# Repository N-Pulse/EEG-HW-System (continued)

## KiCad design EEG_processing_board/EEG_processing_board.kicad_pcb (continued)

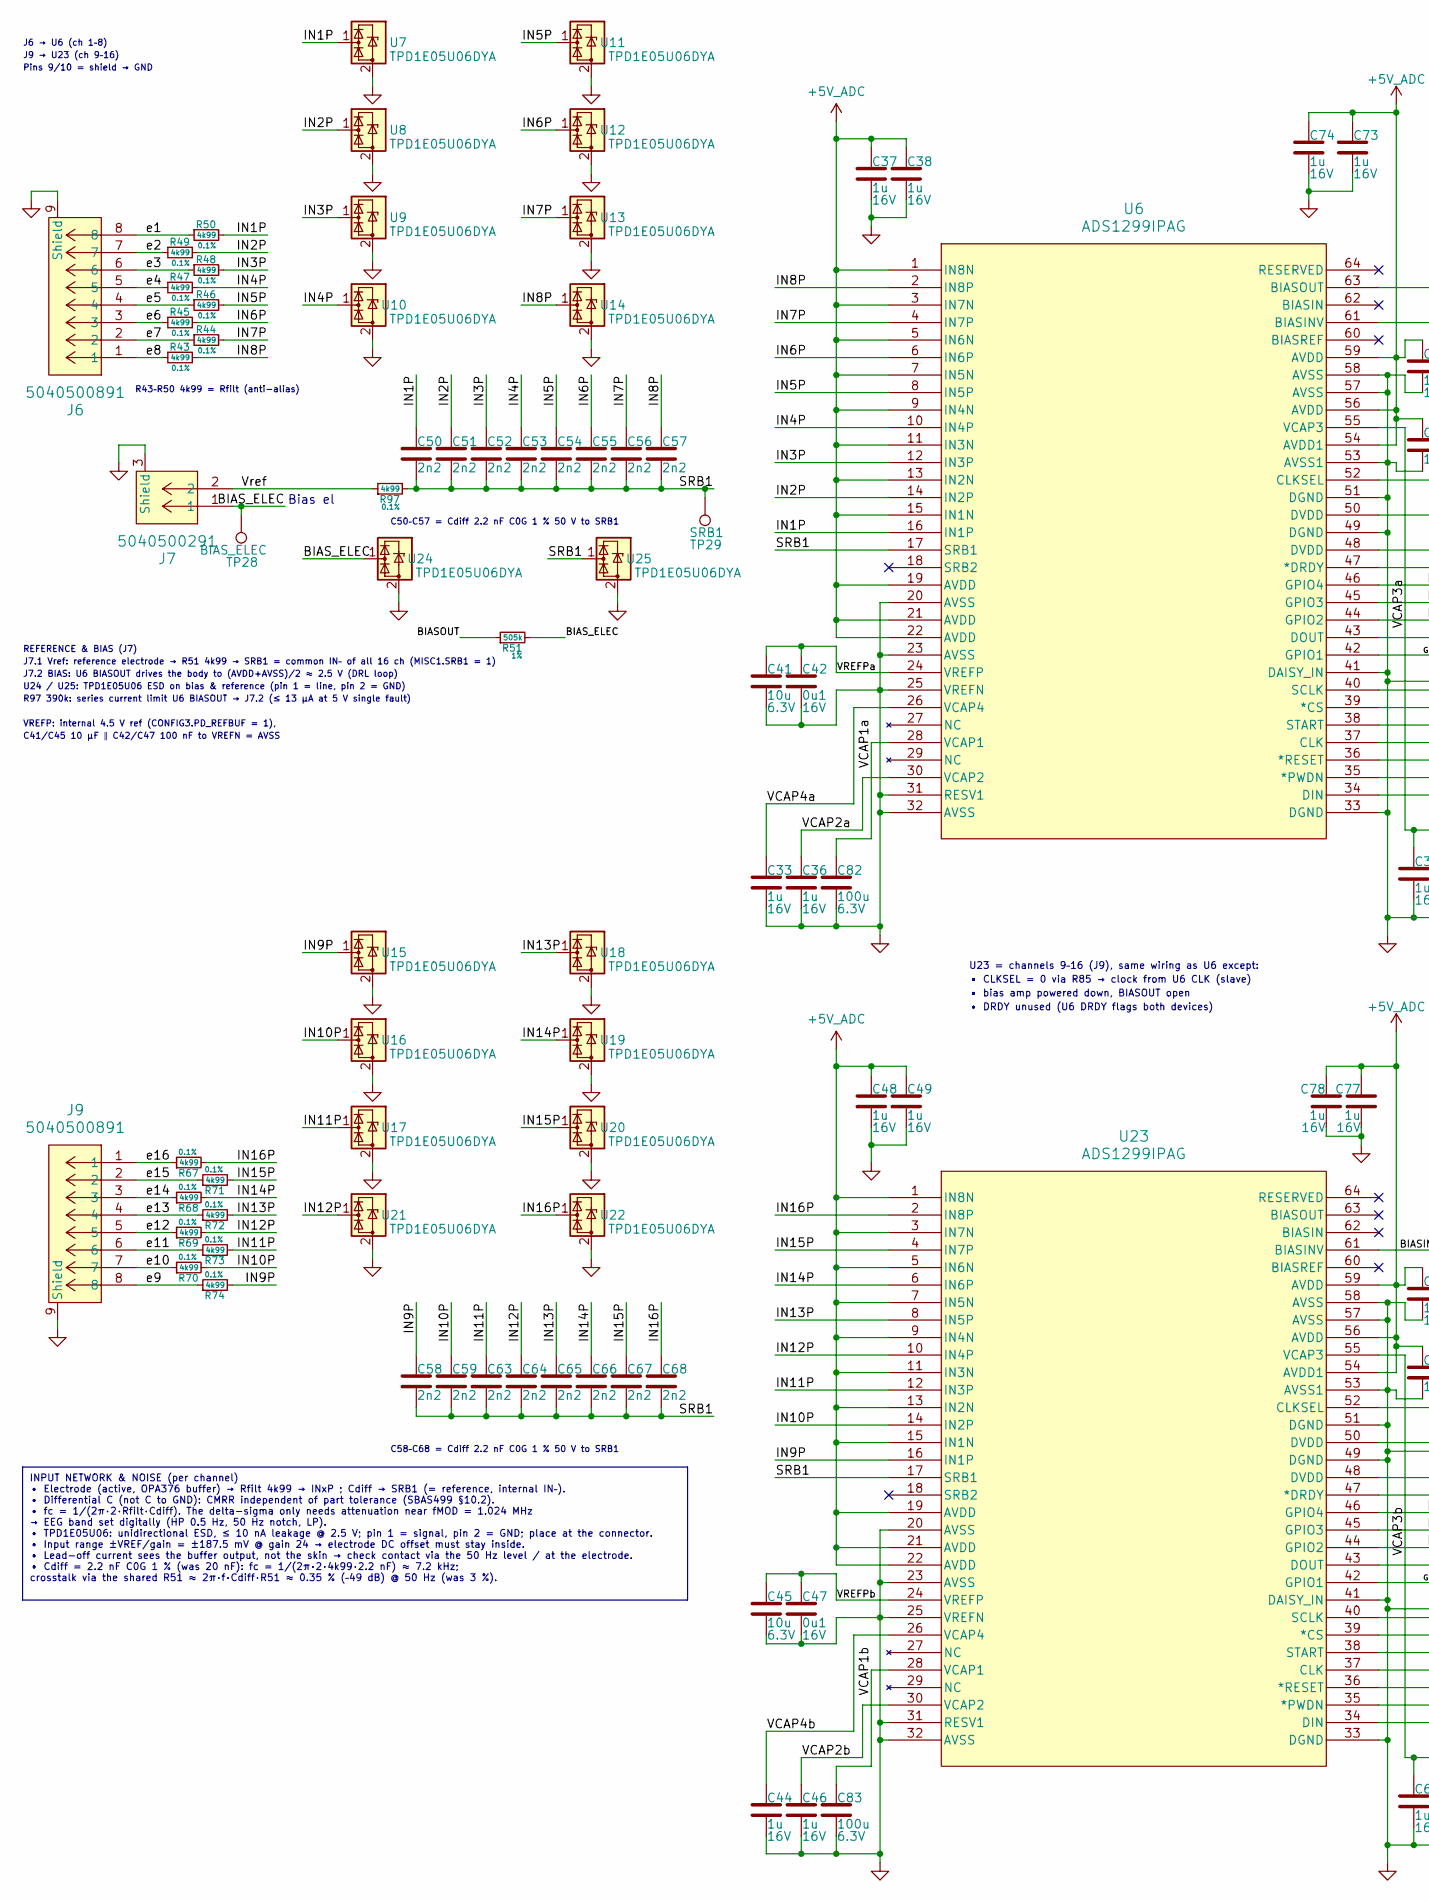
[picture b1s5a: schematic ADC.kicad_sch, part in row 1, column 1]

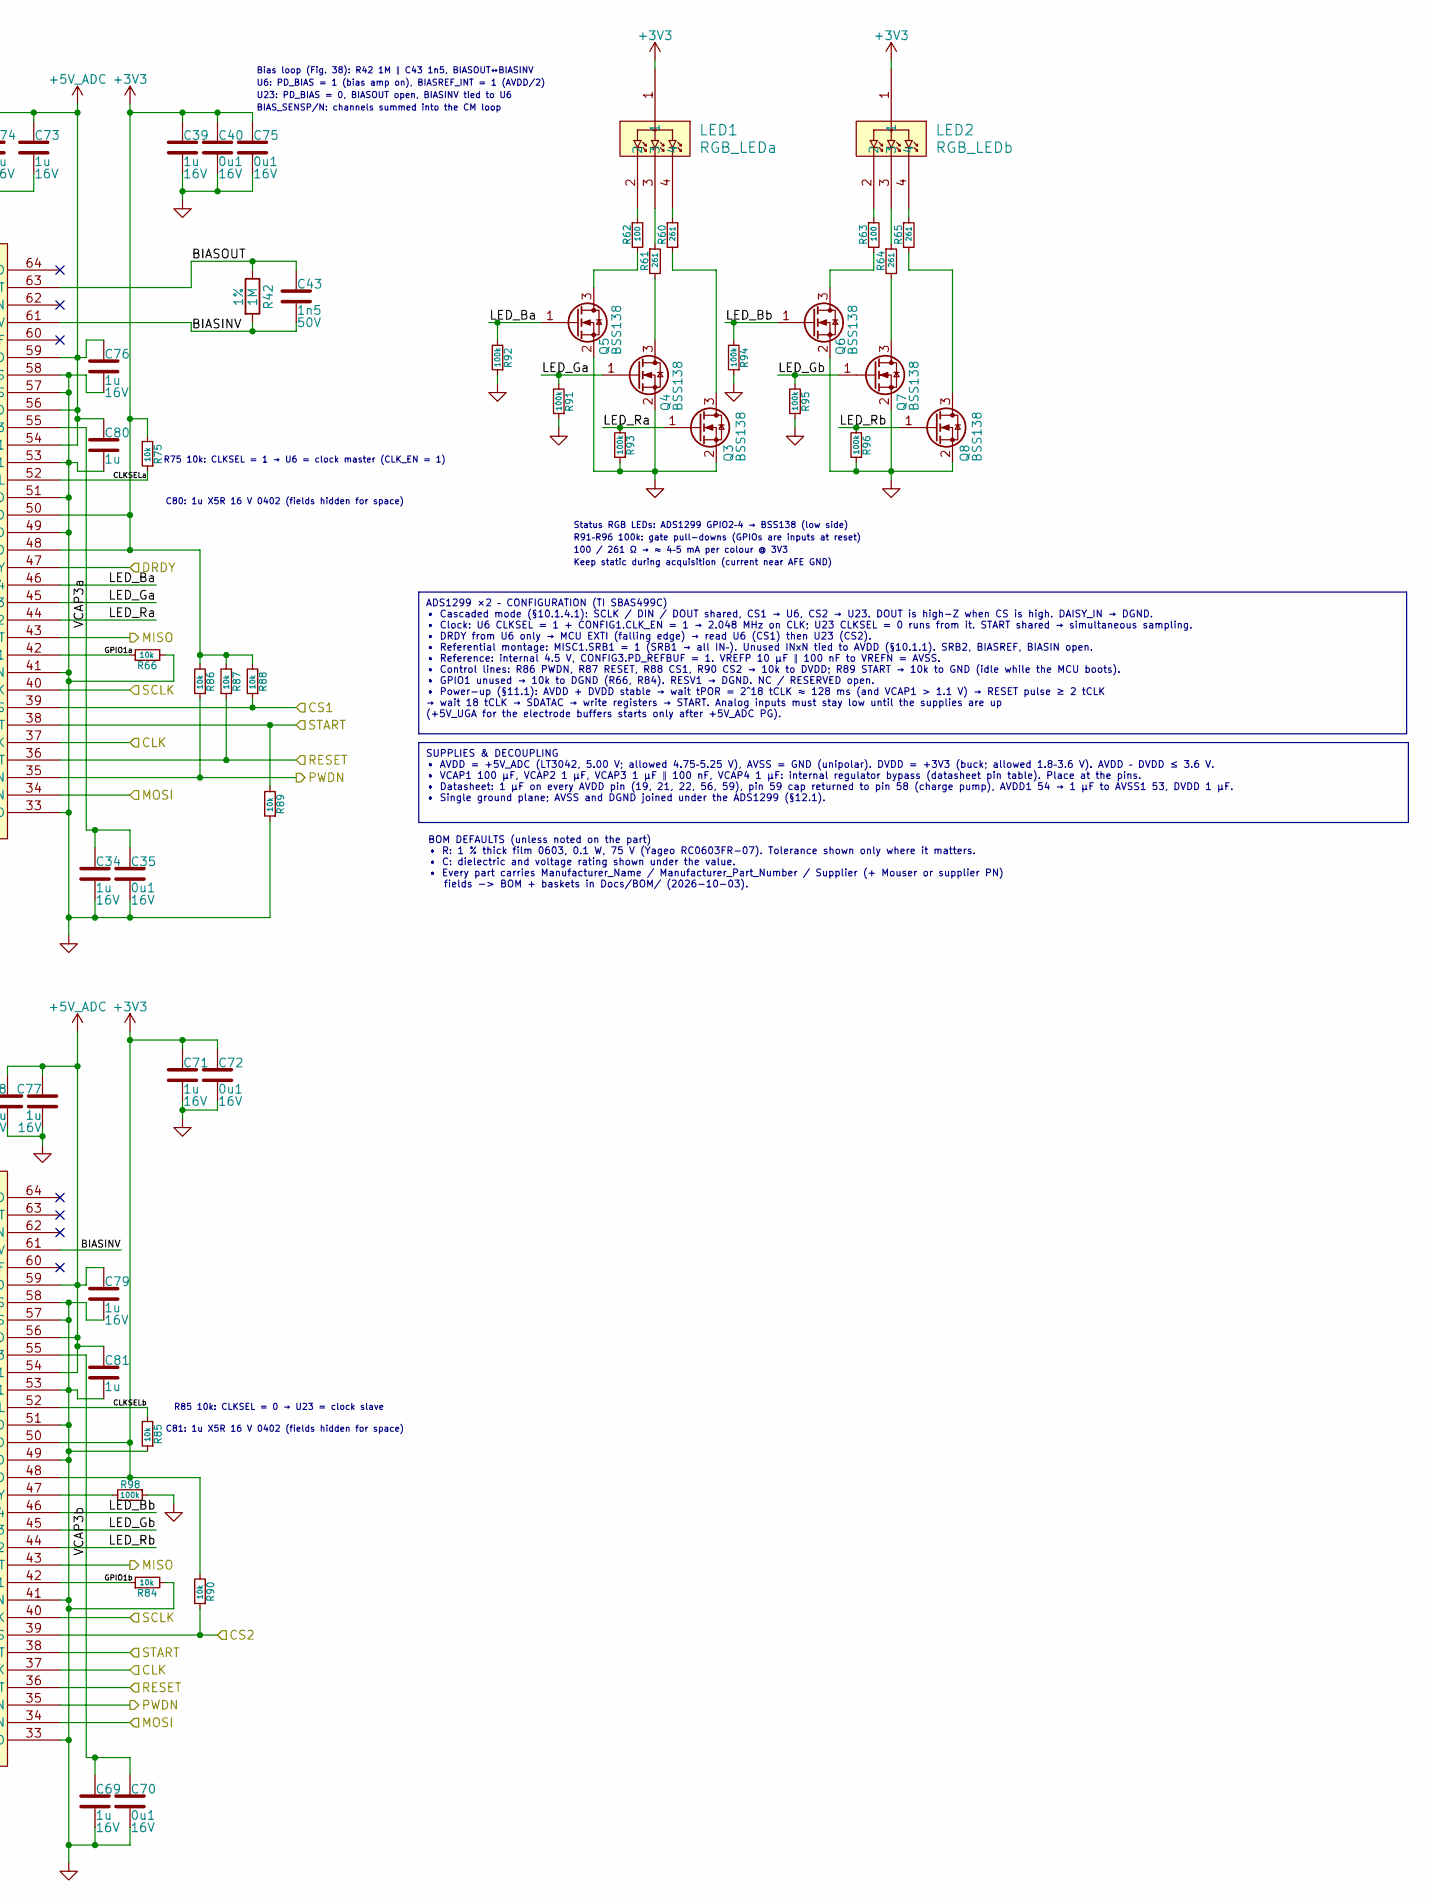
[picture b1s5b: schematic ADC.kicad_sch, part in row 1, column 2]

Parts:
C33, C34, C36, C37, C38, C39, C44, C46, C48, C49, C69, C71, C73, C74, C76, C77, C78, C79, C80, C81: 1u; C_0402_1005Metric; Rating 16V; Tolerance 10%; Manufacturer_Part_Number CL05A105KO5NNNC
C35, C40, C42, C47, C70, C72, C75: 0u1; C_0402_1005Metric; Rating 16V; Tolerance 10%; Manufacturer_Part_Number CC0402KRX7R7BB104
C41, C45: 10u; C_0402_1005Metric; Rating 6.3V; Tolerance 20%; Manufacturer_Part_Number GRM155R60J106ME15D
C43: 1n5; C_0402_1005Metric; Rating 50V; Tolerance 5%; Manufacturer_Part_Number GRM1555C1H152JA01D
C50, C51, C52, C53, C54, C55, C56, C57, C58, C59, C63, C64, C65, C66, C67, C68: 2n2; C_0603_1608Metric; Rating 50V; Tolerance 1%; Manufacturer_Part_Number CC0603FRNPO9BN222
C82, C83: 100u; C_1206_3216Metric; Rating 6.3V; Tolerance 20%; Manufacturer_Part_Number C3216X5R0J107M160AB
J6, J9: 5040500891; CONN_5040500891_MOL
J7: 5040500291; CONN_5040500291_MOL
LED1: RGB_LEDa; CLMVC-FKA-CL1D1L71BB7C3C3_CRE; Manufacturer_Part_Number CLMVC-FKA-CL1D1L71BB7C3C3
LED2: RGB_LEDb; CLMVC-FKA-CL1D1L71BB7C3C3_CRE; Manufacturer_Part_Number CLMVC-FKA-CL1D1L71BB7C3C3
Q3, Q4, Q5, Q6, Q7, Q8: BSS138; SOT-23; Rating N-ch 50V 0.2A; Manufacturer_Part_Number BSS138LT1G
R42: 1M; R_0603_1608Metric; Tolerance 1%; Rating 0.1W; Manufacturer_Part_Number RC0603FR-071ML; Mouser Part Number 603-RC0603FR-071ML
R43, R44, R45, R46, R47, R48, R49, R50, R67, R68, R69, R70, R71, R72, R73, R74, R97: 4k99; R_0603_1608Metric; Tolerance 0.1%; Rating 0.1W; Manufacturer_Part_Number RT0603BRD074K99L; Mouser Part Number 603-RT0603BRD074K99L
R51: 505k; R_0603_1608Metric; Tolerance 1%; Rating 0.1W; Manufacturer_Part_Number RC0603FR-07390KL; Mouser Part Number 603-RC0603FR-07390KL
R60, R61, R64, R65: 261; R_0603_1608Metric; Tolerance 1%; Rating 0.1W; Manufacturer_Part_Number RC0603FR-07261RL; Mouser Part Number 603-RC0603FR-07261RL
R62, R63: 100; R_0603_1608Metric; Tolerance 1%; Rating 0.1W; Manufacturer_Part_Number RC0603FR-07100RL; Mouser Part Number 603-RC0603FR-07100RL
R66, R75, R84, R85, R86, R87, R88, R89, R90: 10k; R_0603_1608Metric; Tolerance 1%; Rating 0.1W; Manufacturer_Part_Number RC0603FR-0710KL; Mouser Part Number 603-RC0603FR-0710KL
R91, R92, R93, R94, R95, R96: 100k; R_0603_1608Metric; Tolerance 1%; Rating 0.1W; Manufacturer_Part_Number RC0603FR-07100KL; Mouser Part Number 603-RC0603FR-07100KL
R98: 100k; R_0603_1608Metric; Tolerance 1%; Rating 0.1W; Manufacturer_Part_Number RC0603FR-0710KL; Mouser Part Number 603-RC0603FR-0710KL
TP28: BIAS_ELEC; TestPoint_Pad_D1.5mm
TP29: SRB1; TestPoint_THTPad_D2.0mm_Drill1.0mm
U6, U23: ADS1299IPAG; PAG64_TEX; Manufacturer_Part_Number ADS1299IPAG
U7, U8, U9, U10, U11, U12, U13, U14, U15, U16, U17, U18, U19, U20, U21, U22, U24, U25: TPD1E05U06DYA; D_SOD-523; Manufacturer_Part_Number TPD1E05U06DYAR

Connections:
+3V3: C39.1, C40.1, C71.1, C72.1, C75.1, LED1.1, LED2.1, R75.2, R86.2, R87.2, R88.2, R90.2, U6.48 (DVDD), U6.50 (DVDD), U23.48 (DVDD), U23.50 (DVDD); also elsewhere on the board
+5V_ADC: C37.1, C38.1, C48.1, C49.1, C73.1, C74.1, C76.1, C77.1, C78.1, C79.1, C80.1, C81.1, U6.1 (IN8N), U6.3 (IN7N), U6.5 (IN6N), U6.7 (IN5N), U6.9 (IN4N), U6.11 (IN3N), U6.13 (IN2N), U6.15 (IN1N), U6.19 (AVDD), U6.21 (AVDD), U6.22 (AVDD), U6.54 (AVDD1), U6.56 (AVDD), U6.59 (AVDD), U23.1 (IN8N), U23.3 (IN7N), U23.5 (IN6N), U23.7 (IN5N), U23.9 (IN4N), U23.11 (IN3N), U23.13 (IN2N), U23.15 (IN1N), U23.19 (AVDD), U23.21 (AVDD), U23.22 (AVDD), U23.54 (AVDD1), U23.56 (AVDD), U23.59 (AVDD); also elsewhere on the board
/Architecture/ADC/BIASINV: C43.2, R42.2, U6.61 (BIASINV), U23.61 (BIASINV)
/Architecture/ADC/BIASOUT: C43.1, R42.1, R51.1, U6.63 (BIASOUT)
/Architecture/ADC/BIAS_ELEC: J7.1, R51.2, TP28.1 (1_1), U24.1 (I/O)
/Architecture/ADC/CLK: U6.37 (CLK), U23.37 (CLK); also elsewhere on the board
/Architecture/ADC/CLKSELa: R75.1, U6.52 (CLKSEL)
/Architecture/ADC/CLKSELb: R85.2, U23.52 (CLKSEL)
/Architecture/ADC/CS1: R88.1, U6.39 (*CS); also elsewhere on the board
/Architecture/ADC/CS2: R90.1, U23.39 (*CS); also elsewhere on the board
/Architecture/ADC/DRDY: U6.47 (*DRDY); also elsewhere on the board
/Architecture/ADC/GPIO1a: R66.1, U6.42 (GPIO1)
/Architecture/ADC/GPIO1b: R84.1, U23.42 (GPIO1)
/Architecture/ADC/IN1P: C50.1, R50.2, U6.16 (IN1P), U7.1 (I/O)
/Architecture/ADC/IN2P: C51.1, R49.2, U6.14 (IN2P), U8.1 (I/O)
/Architecture/ADC/IN3P: C52.1, R48.2, U6.12 (IN3P), U9.1 (I/O)
/Architecture/ADC/IN4P: C53.1, R47.2, U6.10 (IN4P), U10.1 (I/O)
/Architecture/ADC/IN5P: C54.1, R46.2, U6.8 (IN5P), U11.1 (I/O)
/Architecture/ADC/IN6P: C55.1, R45.2, U6.6 (IN6P), U12.1 (I/O)
/Architecture/ADC/IN7P: C56.1, R44.2, U6.4 (IN7P), U13.1 (I/O)
/Architecture/ADC/IN8P: C57.1, R43.2, U6.2 (IN8P), U14.1 (I/O)
/Architecture/ADC/IN9P: C58.1, R74.2, U15.1 (I/O), U23.16 (IN1P)
/Architecture/ADC/IN10P: C59.1, R70.2, U16.1 (I/O), U23.14 (IN2P)
/Architecture/ADC/IN11P: C63.1, R73.2, U17.1 (I/O), U23.12 (IN3P)
/Architecture/ADC/IN12P: C64.1, R69.2, U21.1 (I/O), U23.10 (IN4P)
/Architecture/ADC/IN13P: C65.1, R72.2, U18.1 (I/O), U23.8 (IN5P)
/Architecture/ADC/IN14P: C66.1, R68.2, U19.1 (I/O), U23.6 (IN6P)
/Architecture/ADC/IN15P: C67.1, R71.2, U20.1 (I/O), U23.4 (IN7P)
/Architecture/ADC/IN16P: C68.1, R67.2, U22.1 (I/O), U23.2 (IN8P)
/Architecture/ADC/LED_Ba: Q5.1 (G), R92.2, U6.46 (GPIO4)
/Architecture/ADC/LED_Bb: Q6.1 (G), R94.2, U23.46 (GPIO4)
/Architecture/ADC/LED_Ga: Q4.1 (G), R91.2, U6.45 (GPIO3)
/Architecture/ADC/LED_Gb: Q7.1 (G), R95.2, U23.45 (GPIO3)
/Architecture/ADC/LED_Ra: Q3.1 (G), R93.2, U6.44 (GPIO2)
/Architecture/ADC/LED_Rb: Q8.1 (G), R96.2, U23.44 (GPIO2)
/Architecture/ADC/MISO: U6.43 (DOUT), U23.43 (DOUT); also elsewhere on the board
/Architecture/ADC/MOSI: U6.34 (DIN), U23.34 (DIN); also elsewhere on the board
/Architecture/ADC/PWDN: R86.1, U6.35 (*PWDN), U23.35 (*PWDN); also elsewhere on the board
/Architecture/ADC/RESET: R87.1, U6.36 (*RESET), U23.36 (*RESET); also elsewhere on the board
/Architecture/ADC/SCLK: U6.40 (SCLK), U23.40 (SCLK); also elsewhere on the board
/Architecture/ADC/SRB1: C50.2, C51.2, C52.2, C53.2, C54.2, C55.2, C56.2, C57.2, C58.2, C59.2, C63.2, C64.2, C65.2, C66.2, C67.2, C68.2, R97.2, TP29.1 (1_1), U6.17 (SRB1), U23.17 (SRB1), U25.1 (I/O)
/Architecture/ADC/START: R89.2, U6.38 (START), U23.38 (START); also elsewhere on the board
/Architecture/ADC/VCAP1a: C82.1, U6.28 (VCAP1)
/Architecture/ADC/VCAP1b: C83.1, U23.28 (VCAP1)
/Architecture/ADC/VCAP2a: C36.1, U6.30 (VCAP2)
/Architecture/ADC/VCAP2b: C46.1, U23.30 (VCAP2)
/Architecture/ADC/VCAP3a: C34.1, C35.1, U6.55 (VCAP3)
/Architecture/ADC/VCAP3b: C69.1, C70.1, U23.55 (VCAP3)
/Architecture/ADC/VCAP4a: C33.1, U6.26 (VCAP4)
/Architecture/ADC/VCAP4b: C44.1, U23.26 (VCAP4)
/Architecture/ADC/VREFPa: C41.1, C42.1, U6.24 (VREFP)
/Architecture/ADC/VREFPb: C45.1, C47.1, U23.24 (VREFP)
/Architecture/ADC/Vref: J7.2, R97.1
/Architecture/ADC/e1: J6.8, R50.1
/Architecture/ADC/e2: J6.7, R49.1
/Architecture/ADC/e3: J6.6, R48.1
/Architecture/ADC/e4: J6.5, R47.1
/Architecture/ADC/e5: J6.4, R46.1
/Architecture/ADC/e6: J6.3, R45.1
/Architecture/ADC/e7: J6.2, R44.1
/Architecture/ADC/e8: J6.1, R43.1
/Architecture/ADC/e9: J9.8, R74.1
/Architecture/ADC/e10: J9.7, R70.1
/Architecture/ADC/e11: J9.6, R73.1
/Architecture/ADC/e12: J9.5, R69.1
/Architecture/ADC/e13: J9.4, R72.1
/Architecture/ADC/e14: J9.3, R68.1
/Architecture/ADC/e15: J9.2, R71.1
/Architecture/ADC/e16: J9.1, R67.1
GND: C33.2, C34.2, C35.2, C36.2, C37.2, C38.2, C39.2, C40.2, C41.2, C42.2, C44.2, C45.2, C46.2, C47.2, C48.2, C49.2, C69.2, C70.2, C71.2, C72.2, C73.2, C74.2, C75.2, C76.2, C77.2, C78.2, C79.2, C80.2, C81.2, C82.2, C83.2, J6.9 (Shield), J6.10 (Shield), J7.3 (Shield), J7.4 (Shield), J9.9 (Shield), J9.10 (Shield), Q3.2 (S), Q4.2 (S), Q5.2 (S), Q6.2 (S), Q7.2 (S), Q8.2 (S), R66.2, R84.2, R85.1, R89.1, R91.1, R92.1, R93.1, R94.1, R95.1, R96.1, R98.1, U6.20 (AVSS), U6.23 (AVSS), U6.25 (VREFN), U6.31 (RESV1), U6.32 (AVSS), U6.33 (DGND), U6.41 (DAISY_IN), U6.49 (DGND), U6.51 (DGND), U6.53 (AVSS1), U6.57 (AVSS), U6.58 (AVSS), U7.2 (GND), U8.2 (GND), U9.2 (GND), U10.2 (GND), U11.2 (GND), U12.2 (GND), U13.2 (GND), U14.2 (GND), U15.2 (GND), U16.2 (GND), U17.2 (GND), U18.2 (GND), U19.2 (GND), U20.2 (GND), U21.2 (GND), U22.2 (GND), U23.20 (AVSS), U23.23 (AVSS), U23.25 (VREFN), U23.31 (RESV1), U23.32 (AVSS), U23.33 (DGND), U23.41 (DAISY_IN), U23.49 (DGND), U23.51 (DGND), U23.53 (AVSS1), U23.57 (AVSS), U23.58 (AVSS), U24.2 (GND), U25.2 (GND); also elsewhere on the board
unnamed: LED1.2, R62.1
unnamed: LED1.3, R61.1
unnamed: LED1.4, R60.1
unnamed: LED2.2, R63.1
unnamed: LED2.3, R64.1
unnamed: LED2.4, R65.1
unnamed: Q3.3 (D), R60.2
unnamed: Q4.3 (D), R61.2
unnamed: Q5.3 (D), R62.2
unnamed: Q6.3 (D), R63.2
unnamed: Q7.3 (D), R64.2
unnamed: Q8.3 (D), R65.2
unnamed: R98.2, U23.47 (*DRDY)

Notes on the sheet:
• DRDY unused (U6 DRDY flags both devices)
C41/C45 10 µF ∥ C42/C47 100 nF to VREFN = AVSS
J7.1 Vref: reference electrode → R51 4k99 → SRB1 = common IN– of all 16 ch (MISC1.SRB1 = 1)
100 / 261 Ω → ≈ 4–5 mA per colour @ 3V3
J7.2 BIAS: U6 BIASOUT drives the body to (AVDD+AVSS)/2 ≈ 2.5 V (DRL loop)
U24 / U25: TPD1E05U06 ESD on bias & reference (pin 1 = line, pin 2 = GND)
REFERENCE & BIAS (J7)
VREFP: internal 4.5 V ref (CONFIG3.PD_REFBUF = 1),
Keep static during acquisition (current near AFE GND)
Status RGB LEDs: ADS1299 GPIO2–4 → BSS138 (low side)
C81: 1u X5R 16 V 0402 (fields hidden for space)
R75 10k: CLKSEL = 1 → U6 = clock master (CLK_EN = 1)
U23 = channels 9–16 (J9), same wiring as U6 except:
C50–C57 = Cdiff 2.2 nF C0G 1 % 50 V to SRB1
C80: 1u X5R 16 V 0402 (fields hidden for space)
J6 → U6 (ch 1–8)
• bias amp powered down, BIASOUT open
Pins 9/10 = shield → GND
C58–C68 = Cdiff 2.2 nF C0G 1 % 50 V to SRB1
Bias el
R85 10k: CLKSEL = 0 → U23 = clock slave
R97 390k: series current limit U6 BIASOUT → J7.2 (≤ 13 µA at 5 V single fault)
U6: PD_BIAS = 1 (bias amp on), BIASREF_INT = 1 (AVDD/2)
Bias loop (Fig. 38): R42 1M ∥ C43 1n5, BIASOUT↔BIASINV
• CLKSEL = 0 via R85 → clock from U6 CLK (slave)
BIAS_SENSP/N: channels summed into the CM loop
R43–R50 4k99 = Rfilt (anti-alias)
R91–R96 100k: gate pull-downs (GPIOs are inputs at reset)
U23: PD_BIAS = 0, BIASOUT open, BIASINV tied to U6
BOM DEFAULTS (unless noted on the part) • R: 1 % thick film 0603, 0.1 W, 75 V (Yageo RC0603FR-07). Tolerance shown only where it matters. • C: dielectric and voltage rating shown under the value. • Every part carries Manufacturer_Name / Manufacturer_Part_Number / Supplier (+ Mouser or supplier PN) 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
J9 → U23 (ch 9–16)
INPUT NETWORK & NOISE (per channel) • Electrode (active, OPA376 buffer) → Rfilt 4k99 → INxP ; Cdiff → SRB1 (= reference, internal IN–). • Differential C (not C to GND): CMRR independent of part tolerance (SBAS499 §10.2). • fc = 1/(2π·2·Rfilt·Cdiff). The delta-sigma only needs attenuation near fMOD 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
SUPPLIES & DECOUPLING • AVDD = +5V_ADC (LT3042, 5.00 V; allowed 4.75–5.25 V), AVSS = GND (unipolar). DVDD = +3V3 (buck; allowed 1.8–3.6 V). AVDD – DVDD ≤ 3.6 V. • VCAP1 100 µF, VCAP2 1 µF, VCAP3 1 µF ∥ 100 nF, VCAP4 1 µF: internal regulator bypass (datasheet pin table). Place at the pins. • Datashe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
ADS1299 ×2 – CONFIGURATION (TI SBAS499C) • Cascaded mode (§10.1.4.1): SCLK / DIN / DOUT shared, CS1 → U6, CS2 → U23. DOUT is high-Z when CS is high. DAISY_IN → DGND. • Clock: U6 CLKSEL = 1 + CONFIG1.CLK_EN = 1 → 2.048 MHz on CLK; U23 CLKSEL = 0 runs from it. START shared → simultaneous sampling. • 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

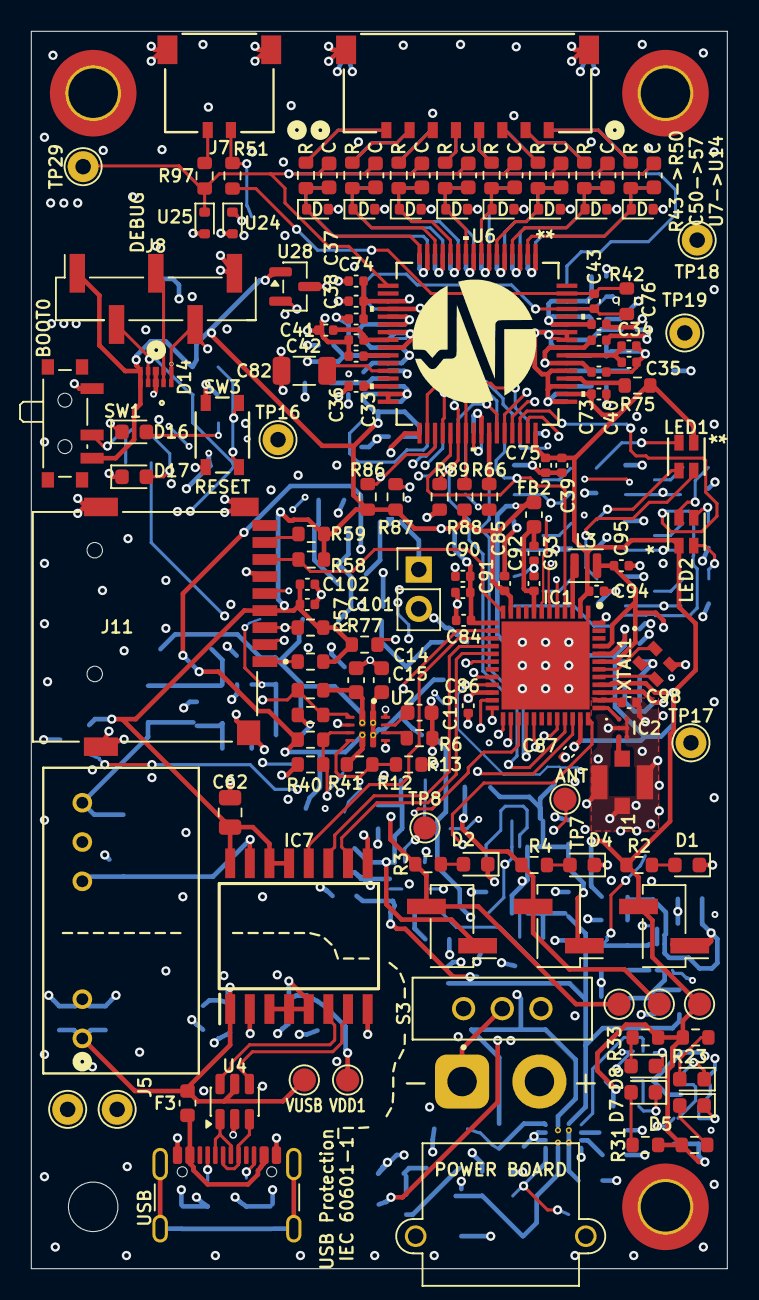
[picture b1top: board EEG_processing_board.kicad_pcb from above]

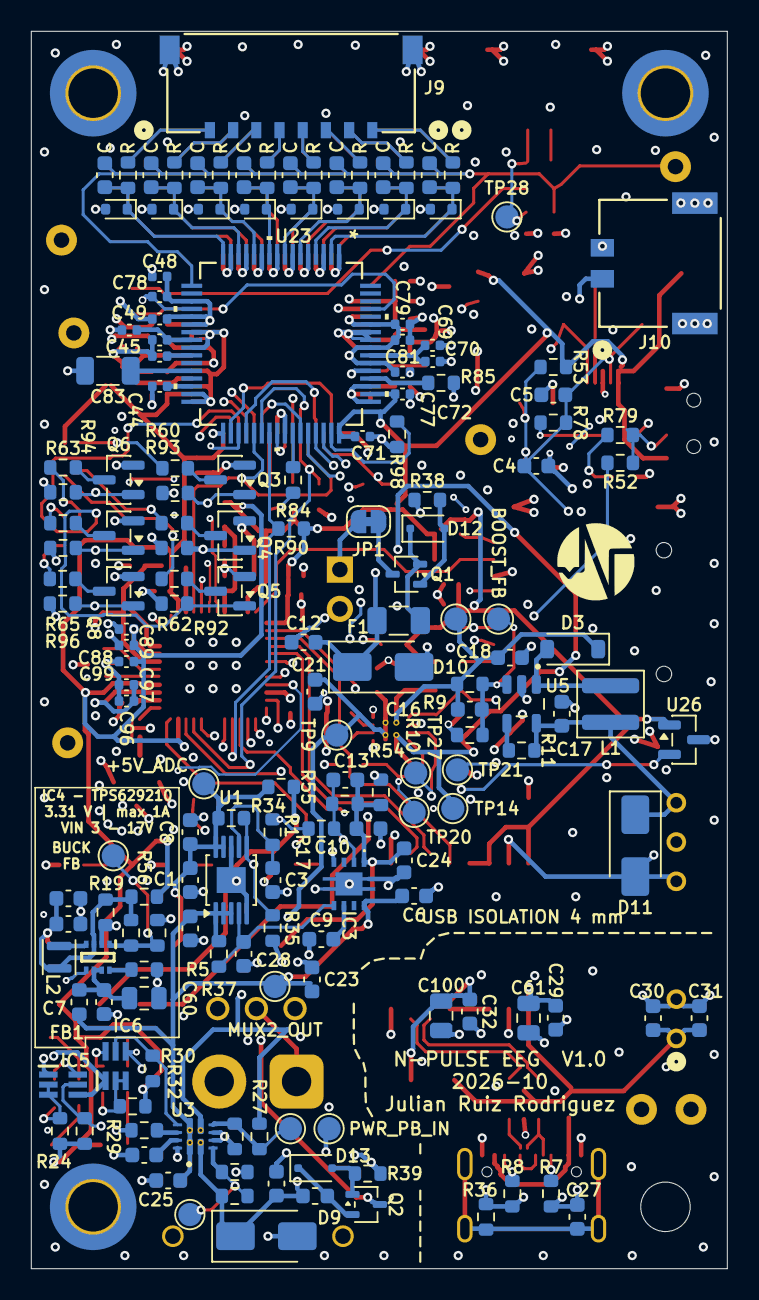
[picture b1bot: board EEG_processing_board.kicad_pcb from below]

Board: 4 copper layers, 45.0 x 80.0 mm, 315 parts (171 on the bottom side), 173 nets.

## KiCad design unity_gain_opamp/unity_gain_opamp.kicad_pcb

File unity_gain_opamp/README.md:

# N-Pulse Workshop Board

A teaching board for the N-Pulse electronics workshop: an ESP32-S3 platform with
a complete battery power path, four sensors, and a heart-rate (PPG) front end —
designed so that new members can learn hardware design by reading a real,
working board rather than a toy example.

## What this board is for

Most beginner projects are one circuit. This board is deliberately the opposite:
it puts one worked example of nearly every subsystem you meet in real hardware
onto a single PCB, so that "how do I charge a battery?", "how do I protect a USB
port?" or "how do I amplify a microvolt sensor?" all have an answer you can hold
in your hand and probe with a scope.

It is a **reference**, not a first project. Read it, measure it, copy from it.

Every design decision is documented in **[DESIGN_NOTES.md](DESIGN_NOTES.md)**,
which also contains general guidance on how to draw a good schematic and how to
lay out a good PCB.

## Features

**Power**
- USB-C input with ESD protection and a TVS on VBUS
- MCP73833 Li-ion charger (1 A) with charge / done / power-good indicators
- BQ29728 cell protection with back-to-back MOSFETs
- TPS631000 buck-boost — holds 3.3 V across the whole 4.2 → 3.0 V cell range
- TPS2116 priority mux — runs from USB when present, battery otherwise
- TPS2068 load switch — firmware can cut power to the peripherals
- Two rails: `+3V3_ESP32` (always on) and `+3V3` (switched)

**Sensing**
- SHT40 — humidity and temperature (I²C)
- LIS2DW12 — 3-axis accelerometer with interrupts, on the always-on rail so the
  board can wake on motion
- MCP9700A — analog temperature
- PPG pulse sensor — LED + photodiode into a two-stage bandpass amplifier
  (0.34–5 Hz, gain ×121)

**Interfaces**
- ESP32-S3-WROOM-1, programmed over native USB — no bridge chip, no drivers
- microSD card slot with mechanical card detect
- Two RGB LEDs and a piezo buzzer
- I²C expansion header
- 17 labelled test points

**Physical:** 70 × 80 mm, 2-layer, 142 components, four M4 mounting holes.

## Using the board

**Powering it.** Plug in USB-C and it runs, regardless of the ON/OFF switch. On
battery, slide the ON/OFF switch (bottom edge, marked `ON`/`OFF`). With USB
connected the board runs from USB and charges the cell at the same time.

**Charging.** The three LEDs on the left edge are, top to bottom, `CHRG`
(charging), `DONE` (complete) and `PG` (USB power good).

**Programming.** Connect USB-C — the board enumerates directly as an ESP32-S3.
Normally you can just flash it. If you need to force download mode: slide the
`BOOT0` switch (right edge) to the boot position, press `ENABLE` to reset, flash,
then slide it back and reset again. The LED beside the switch shows its position.

**Reading your pulse.** Rest a fingertip on the fingerprint symbol in the middle
of the board, covering the LED and photodiode, with light steady pressure. The
amplifier needs a second or two to settle. Signal quality depends a lot on
contact pressure and ambient light — that is part of what makes it a good
teaching circuit.

**I²C expansion.** The 4-pin header on the right edge is `3V3 / SDA / SCL / GND`
(labelled on the silkscreen). It is ESD-protected and shares the bus with the
on-board sensors, so remember the address space is shared.

**Test points.** Every rail and every interesting node is brought out:
`+5V USB`, `3V3 USB`, `3V3 BATT`, `3V3 ESP32`, `3V3`, `+BATT`, `-BATT`, `GND`,
plus `FB`, `PR1`, `MODE` and `PWR SW` for the power circuits.

## Opening the project

Built with **KiCad 9/10**. Clone and open `Electronics_Workwhop_PCB.kicad_pro`.

All custom symbols and footprints live in the repository — `N_pulse.pretty/` for
footprints and `Library/` for vendor symbol libraries — so the project should
open with no missing parts. Nothing needs to be installed globally.

```
Electronics_Workwhop_PCB.kicad_pro   project file — open this
├── Architecture.kicad_sch           top-level sheet
├── ESP32.kicad_sch                  MCU, SD card, LEDs, buzzer, buttons
├── Power_management.kicad_sch       USB-C, charger, protection, regulators
├── Sensors.kicad_sch                SHT40, accelerometer, temperature, PPG
└── Electronics_Workwhop_PCB.kicad_pcb
DESIGN_NOTES.md                      why the circuits look the way they do
docs/                                images and documentation assets
```

## Pin map

See [Appendix A of DESIGN_NOTES.md](DESIGN_NOTES.md) for the full table,
generated from the netlist.

The one rule worth memorising: **analog inputs must be on ADC1 (IO1–IO10)**.
ADC2 cannot be read while Wi-Fi is running.

## Contributing

KiCad files cannot be merged. If two people edit the same sheet at the same
time, git produces a conflict that no one can resolve by hand.

Before you start work, say which sheet you are taking, and pull before you open
the project. Commit with a message describing the change, not just "update".

The pre-fabrication checklist in
[Appendix B of DESIGN_NOTES.md](DESIGN_NOTES.md) should be run before any board
is ordered.

---

> *"What I cannot create, I do not understand."* — Richard Feynman
>
> (also printed on the board)

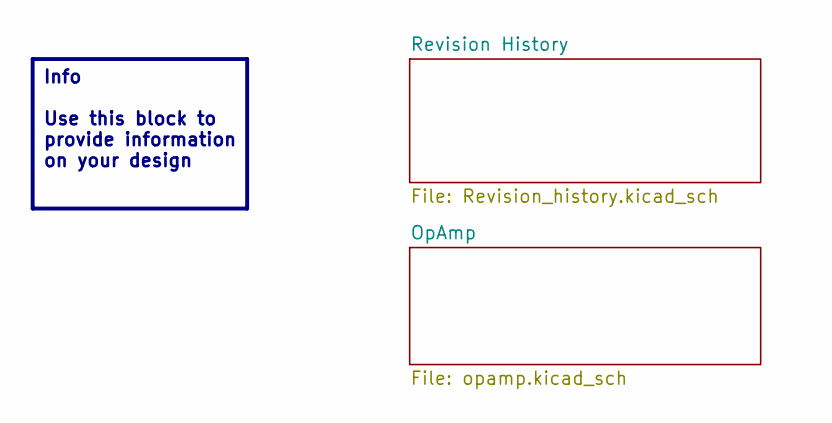
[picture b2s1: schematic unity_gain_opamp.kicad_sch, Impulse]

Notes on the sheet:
Info Use this block to provide information on your design

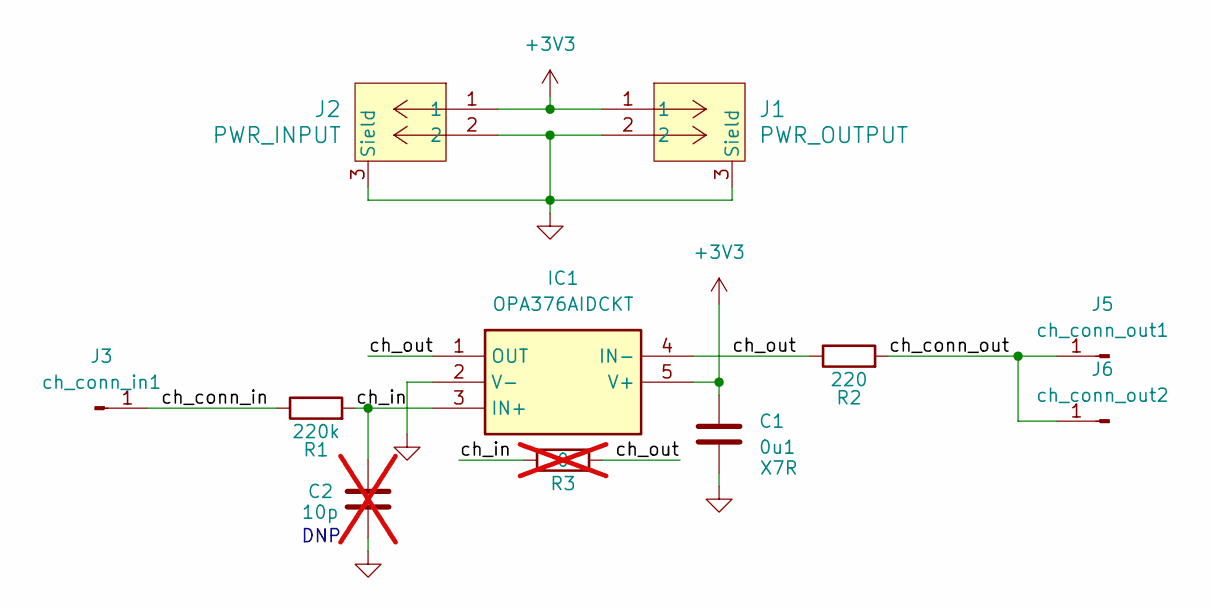
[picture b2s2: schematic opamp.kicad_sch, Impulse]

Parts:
C1: 0u1; C_0805_2012Metric
C2: 10p; C_0805_2012Metric; not fitted
IC1: OPA376AIDCKT; SOT-353_SC-70-5; Manufacturer_Part_Number OPA376AIDCKT
J1: PWR_OUTPUT; CONN_5037630000-SD_02_MOL
J2: PWR_INPUT; CONN_5037630000-SD_02_MOL
J3: ch_conn_in1; electrode
J5: ch_conn_out1; SolderWire-0.75sqmm_1x01_D1.25mm_OD2.3mm_Relief
J6: ch_conn_out2; PinHeader_1x01_P2.54mm_Horizontal
R1: 220k; R_0805_2012Metric
R2: 220; R_0805_2012Metric
R3: 0; R_0805_2012Metric; not fitted

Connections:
+3V3: C1.1, IC1.5 (V+), J1.1, J2.1
/OpAmp/ch_conn_in: J3.1 (Pin_1_1), R1.1
/OpAmp/ch_conn_out: J5.1 (Pin_1_1), J6.1 (Pin_1_1), R2.2
/OpAmp/ch_in: C2.1, IC1.3 (IN+), R1.2, R3.1
/OpAmp/ch_out: IC1.1 (OUT), IC1.4 (IN-), R2.1, R3.2
GND: C1.2, C2.2, IC1.2 (V-), J1.2, J1.3 (Sield), J1.4 (Sield), J2.2, J2.3 (Sield), J2.4 (Sield)

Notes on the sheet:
DNP

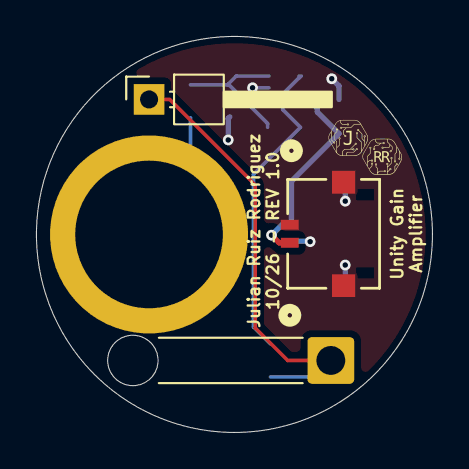
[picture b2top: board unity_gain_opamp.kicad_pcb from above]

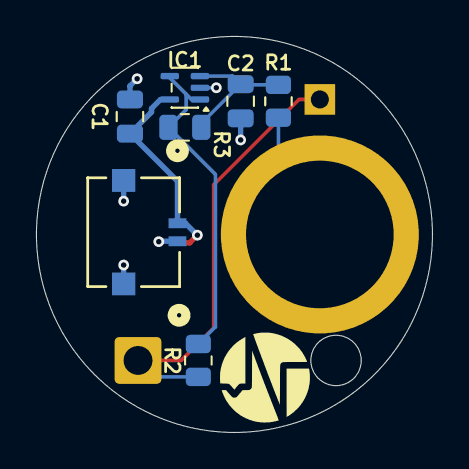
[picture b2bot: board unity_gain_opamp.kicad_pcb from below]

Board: 2 copper layers, 22.0 x 22.0 mm, 11 parts (7 on the bottom side), 6 nets.
